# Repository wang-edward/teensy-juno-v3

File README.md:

# teensy-juno
A Teensy 3.x/4.x based polyphonic synthesizer, modelled after the Juno-106

## Features
- 8 Voice polyphony
- Flanger! 
  - Offset, depth, and rate parameters, and presets
- 
- Pulse, Saw, Sub, and noise oscillators
- HPF and LPF with resonance
- ADSR Envelope
- Pan
- Portamento with variable time
- LFO with delay
- PWM modulation
- VCF mod by Envelope, Lfo and Mod Wheel

## Coming soon?
- hardware
- vcf key tracking?
- moog ladder filter emulation (needs teensy 4.0) 
  - based on (www.researchgate.net/publication/220386519_Oscillator_and_Filter_Algorithms_for_Virtual_Analog_Synthesis)
- filter or regular overdrive
## Notes
don't buy this pcb right now (Dec 2021), there are some errors with clearances lol

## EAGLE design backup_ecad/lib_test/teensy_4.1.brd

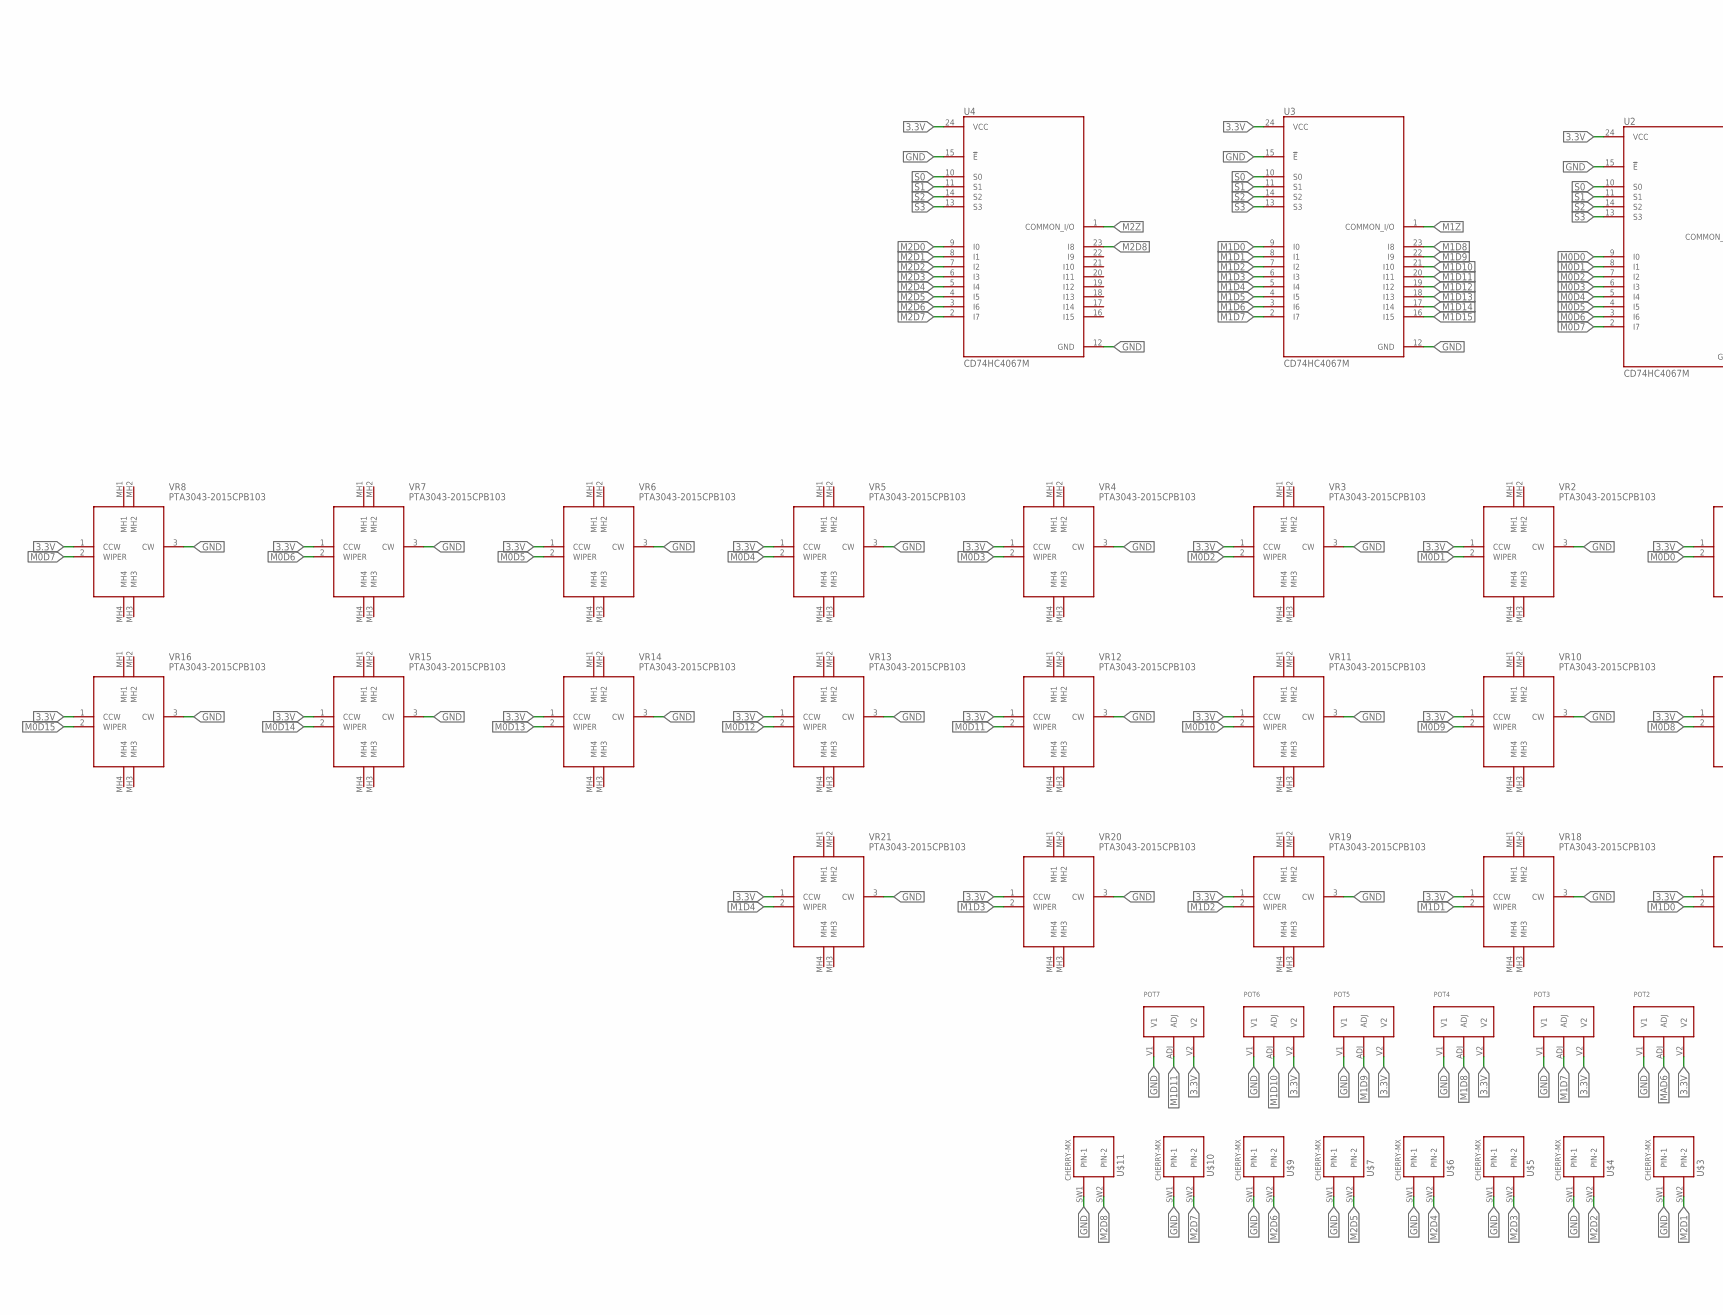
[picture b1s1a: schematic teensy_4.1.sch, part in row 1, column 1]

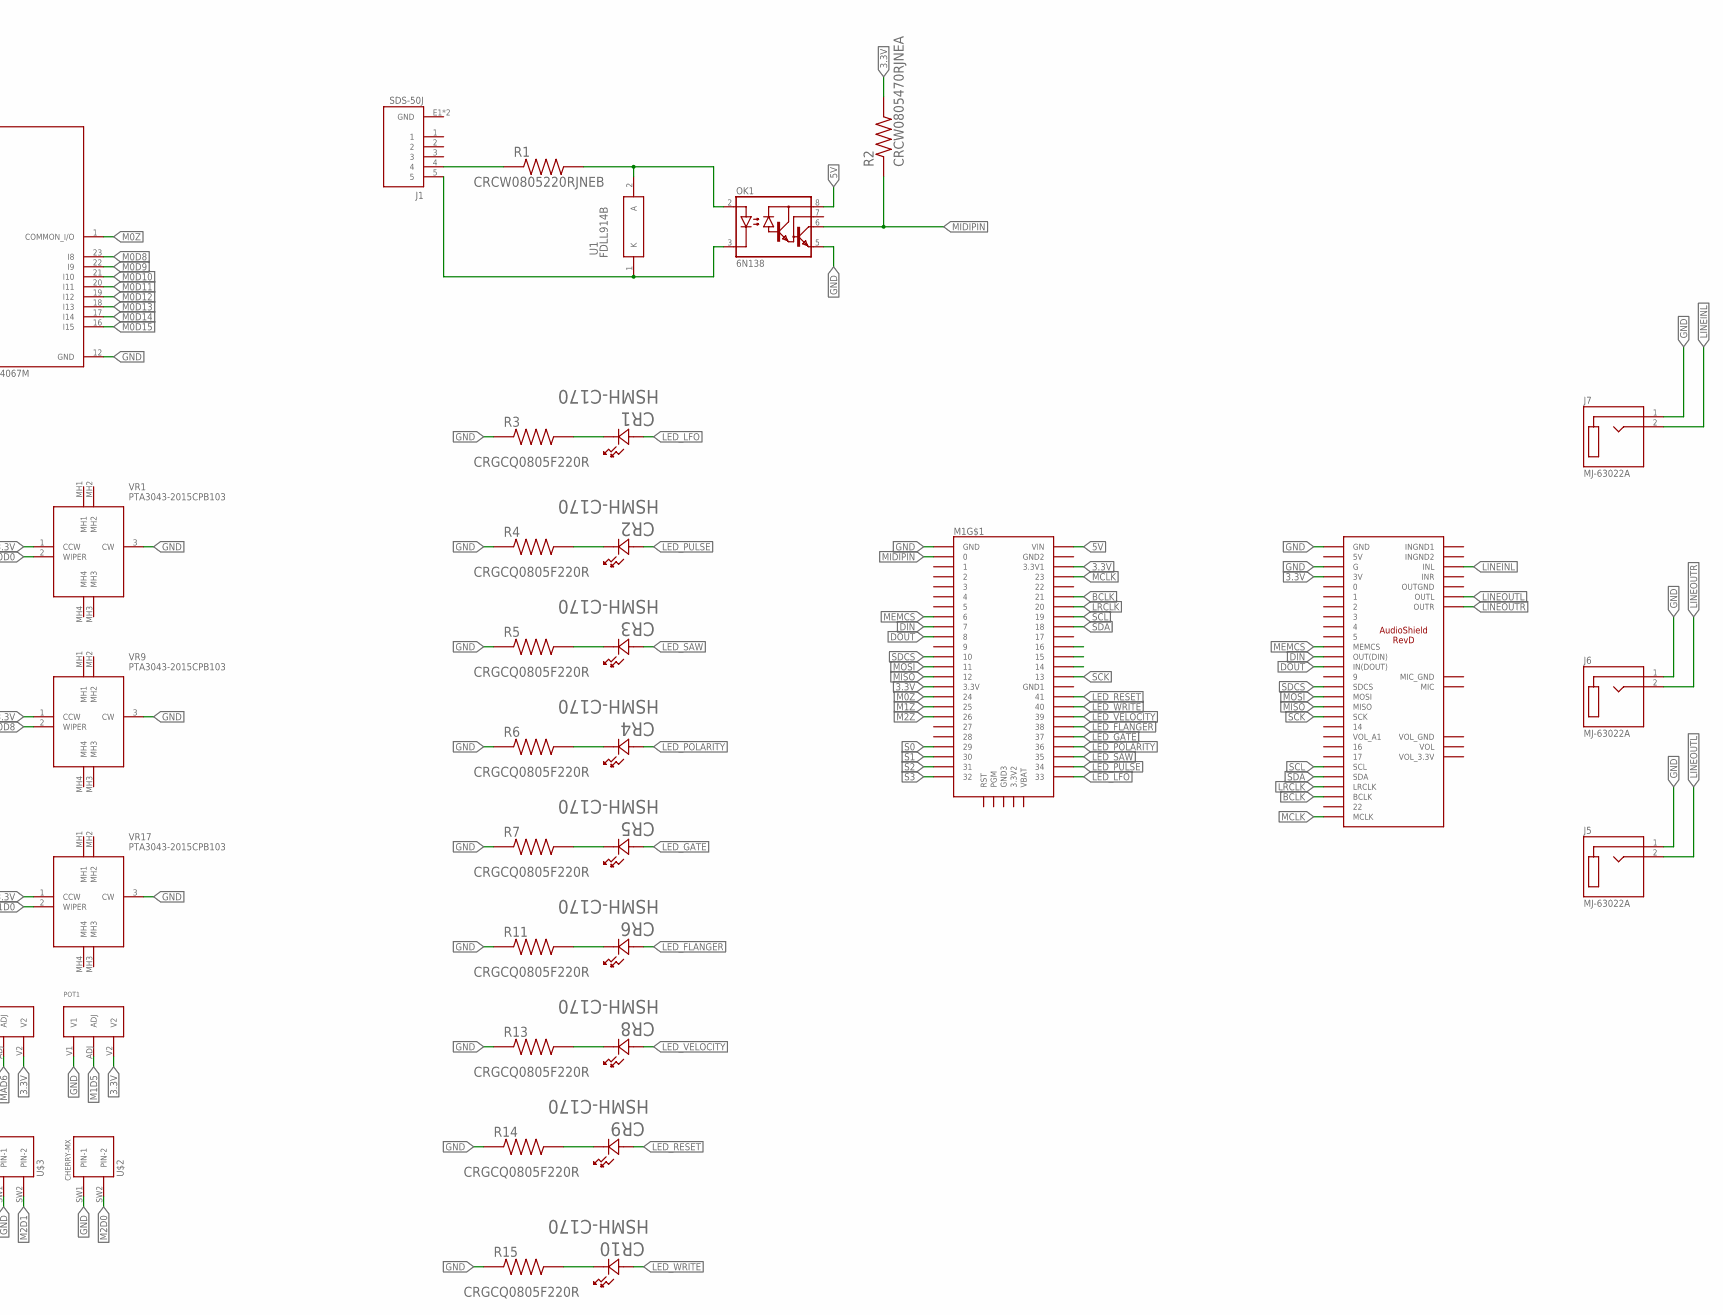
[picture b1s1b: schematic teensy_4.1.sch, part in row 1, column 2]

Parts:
CR1, CR2, CR3, CR4, CR5, CR6, CR8, CR9, CR10: HSMH-C170; LED_HSMX-C170_AVA
J1: SDS-50J; CUI_SDS-50J
J5, J6, J7: MJ-63022A; CUI_MJ-63022A
M1: TEENSY4.1
OK1: 6N138; DIL08
POT1, POT2, POT3, POT4, POT5, POT6, POT7: P0915N_POT; PO915N_POT
R1: CRCW0805220RJNEB; RESC2012X50N
R2: CRCW0805470RJNEA; RESC2012X50N
R3, R4, R5, R6, R7, R11, R13, R14, R15: CRGCQ0805F220R; RESC2012X65N
U1: FDLL914B; SOD-80-2_3P6X1P5_ONS
U2, U3, U4: CD74HC4067M; SOIC127P1030X265-24N
U$1: AUDIOSHIELD-REVD
U$2, U$3, U$4, U$5, U$6, U$7, U$9, U$10, U$11: CHERRY-MX
VR1, VR2, VR3, VR4, VR5, VR6, VR7, VR8, VR9, VR10, VR11, VR12, VR13, VR14, VR15, VR16, VR17, VR18, VR19, VR20, VR21: PTA3043-2015CPB103; PTA30432015CPB103

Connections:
3.3V: M1.3V3 (3.3V), M1.3V3_LO (3.3V1), POT1.V2, POT2.V2, POT3.V2, POT4.V2, POT5.V2, POT6.V2, POT7.V2, R2.2, U2.24 (VCC), U3.24 (VCC), U4.24 (VCC), U$1.3V, VR1.1 (CCW), VR2.1 (CCW), VR3.1 (CCW), VR4.1 (CCW), VR5.1 (CCW), VR6.1 (CCW), VR7.1 (CCW), VR8.1 (CCW), VR9.1 (CCW), VR10.1 (CCW), VR11.1 (CCW), VR12.1 (CCW), VR13.1 (CCW), VR14.1 (CCW), VR15.1 (CCW), VR16.1 (CCW), VR17.1 (CCW), VR18.1 (CCW), VR19.1 (CCW), VR20.1 (CCW), VR21.1 (CCW)
5V: M1.VIN, OK1.8 (VCC)
BCLK: M1.21/A7 (21), U$1.21 (BCLK)
DIN: M1.7, U$1.7 (OUT(DIN))
DOUT: M1.8, U$1.8 (IN(DOUT))
GND: J1.E1 (GND), J1.E2 (GND), J5.1 (SLEEVE), J6.1 (SLEEVE), J7.1 (SLEEVE), M1.GND, OK1.5 (GND), POT1.V1, POT2.V1, POT3.V1, POT4.V1, POT5.V1, POT6.V1, POT7.V1, R3.1, R4.1, R5.1, R6.1, R7.1, R11.1, R13.1, R14.1, R15.1, U2.12 (GND), U2.15 (!E), U3.12 (GND), U3.15 (!E), U4.12 (GND), U4.15 (!E), U$1.G, U$1.GND, U$2.SW1 (PIN-1), U$3.SW1 (PIN-1), U$4.SW1 (PIN-1), U$5.SW1 (PIN-1), U$6.SW1 (PIN-1), U$7.SW1 (PIN-1), U$9.SW1 (PIN-1), U$10.SW1 (PIN-1), U$11.SW1 (PIN-1), VR1.3 (CW), VR2.3 (CW), VR3.3 (CW), VR4.3 (CW), VR5.3 (CW), VR6.3 (CW), VR7.3 (CW), VR8.3 (CW), VR9.3 (CW), VR10.3 (CW), VR11.3 (CW), VR12.3 (CW), VR13.3 (CW), VR14.3 (CW), VR15.3 (CW), VR16.3 (CW), VR17.3 (CW), VR18.3 (CW), VR19.3 (CW), VR20.3 (CW), VR21.3 (CW)
LED_FLANGER: CR6.2, M1.38
LED_GATE: CR5.2, M1.37
LED_LFO: CR1.2, M1.33
LED_POLARITY: CR4.2, M1.36
LED_PULSE: CR2.2, M1.34
LED_RESET: CR9.2, M1.41
LED_SAW: CR3.2, M1.35
LED_VELOCITY: CR8.2, M1.39
LED_WRITE: CR10.2, M1.40
LINEINL: J7.2 (TIP), U$1.INL
LINEOUTL: J5.2 (TIP), U$1.OUTL
LINEOUTR: J6.2 (TIP), U$1.OUTR
LRCLK: M1.20/A6 (20), U$1.20 (LRCLK)
M0D0: U2.9 (I0), VR1.2 (WIPER)
M0D1: U2.8 (I1), VR2.2 (WIPER)
M0D2: U2.7 (I2), VR3.2 (WIPER)
M0D3: U2.6 (I3), VR4.2 (WIPER)
M0D4: U2.5 (I4), VR5.2 (WIPER)
M0D5: U2.4 (I5), VR6.2 (WIPER)
M0D6: U2.3 (I6), VR7.2 (WIPER)
M0D7: U2.2 (I7), VR8.2 (WIPER)
M0D8: U2.23 (I8), VR9.2 (WIPER)
M0D9: U2.22 (I9), VR10.2 (WIPER)
M0D10: U2.21 (I10), VR11.2 (WIPER)
M0D11: U2.20 (I11), VR12.2 (WIPER)
M0D12: U2.19 (I12), VR13.2 (WIPER)
M0D13: U2.18 (I13), VR14.2 (WIPER)
M0D14: U2.17 (I14), VR15.2 (WIPER)
M0D15: U2.16 (I15), VR16.2 (WIPER)
M0Z: M1.24, U2.1 (COMMON_I/O)
M1D0: U3.9 (I0), VR17.2 (WIPER)
M1D1: U3.8 (I1), VR18.2 (WIPER)
M1D2: U3.7 (I2), VR19.2 (WIPER)
M1D3: U3.6 (I3), VR20.2 (WIPER)
M1D4: U3.5 (I4), VR21.2 (WIPER)
M1D5: POT1.ADJ, U3.4 (I5)
M1D6: U3.3 (I6)
M1D7: POT3.ADJ, U3.2 (I7)
M1D8: POT4.ADJ, U3.23 (I8)
M1D9: POT5.ADJ, U3.22 (I9)
M1D10: POT6.ADJ, U3.21 (I10)
M1D11: POT7.ADJ, U3.20 (I11)
M1D12: U3.19 (I12)
M1D13: U3.18 (I13)
M1D14: U3.17 (I14)
M1D15: U3.16 (I15)
M1Z: M1.25, U3.1 (COMMON_I/O)
M2D0: U4.9 (I0), U$2.SW2 (PIN-2)
M2D1: U4.8 (I1), U$3.SW2 (PIN-2)
M2D2: U4.7 (I2), U$4.SW2 (PIN-2)
M2D3: U4.6 (I3), U$5.SW2 (PIN-2)
M2D4: U4.5 (I4), U$6.SW2 (PIN-2)
M2D5: U4.4 (I5), U$7.SW2 (PIN-2)
M2D6: U4.3 (I6), U$9.SW2 (PIN-2)
M2D7: U4.2 (I7), U$10.SW2 (PIN-2)
M2D8: U4.23 (I8), U$11.SW2 (PIN-2)
M2Z: M1.26, U4.1 (COMMON_I/O)
MAD6: POT2.ADJ
MCLK: M1.23/A9 (23), U$1.23 (MCLK)
MEMCS: M1.6, U$1.6 (MEMCS)
MIDIPIN: M1.0/RX (0), OK1.6 (VO), R2.1
MISO: M1.12/MISO (12), U$1.12 (MISO)
MOSI: M1.11/MOSI (11), U$1.11 (MOSI)
unnamed: J1.4, R1.1
unnamed: OK1.2 (A), R1.2, U1.2 (A)
unnamed: J1.5, OK1.3 (C), U1.1 (K)
unnamed: CR2.1, R4.2
unnamed: CR1.1, R3.2
unnamed: CR3.1, R5.2
unnamed: CR4.1, R6.2
unnamed: CR5.1, R7.2
unnamed: CR6.1, R11.2
unnamed: CR8.1, R13.2
unnamed: CR9.1, R14.2
unnamed: CR10.1, R15.2
S0: M1.29, U2.10 (S0), U3.10 (S0), U4.10 (S0)
S1: M1.30, U2.11 (S1), U3.11 (S1), U4.11 (S1)
S2: M1.31/A12 (31), U2.14 (S2), U3.14 (S2), U4.14 (S2)
S3: M1.32, U2.13 (S3), U3.13 (S3), U4.13 (S3)
SCK: M1.13/SCK (13), U$1.13 (SCK)
SCL: M1.19/A5/SCL (19), U$1.19 (SCL)
SDA: M1.18/A4/SDA (18), U$1.18 (SDA)
SDCS: M1.10/CS (10), U$1.10 (SDCS)

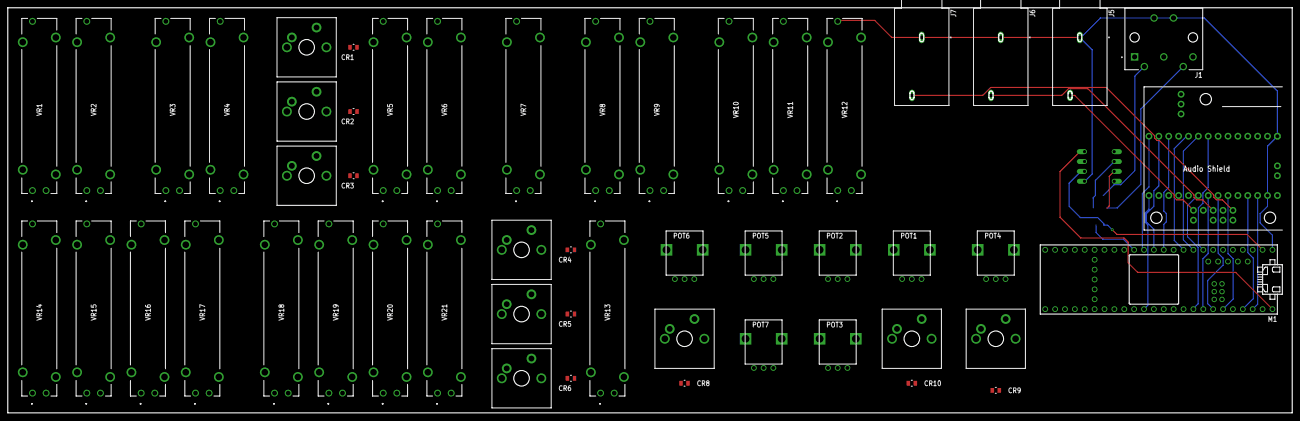
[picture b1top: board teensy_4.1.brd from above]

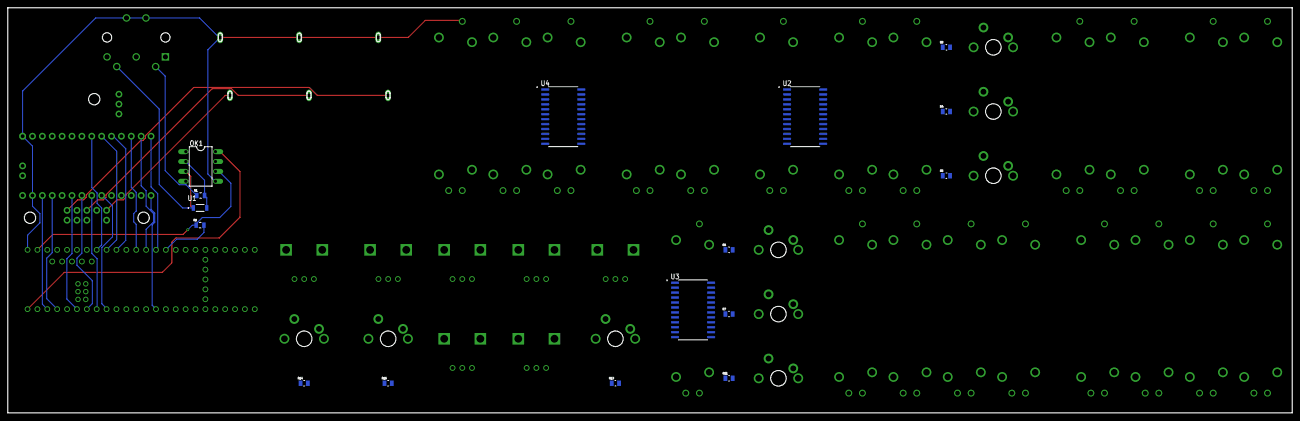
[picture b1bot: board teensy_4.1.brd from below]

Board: 2 copper layers, 330.2 x 104.1 mm, 68 parts (16 on the bottom side), 83 nets.

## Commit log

2021-05-16 starter code (poly note handling) from jmechnich
2021-05-16 modifying starter code
2021-05-17 built new architecture and started on oscillator control
2021-05-18 finished outline of midi and note handling, still broken
2021-05-21 fixed lots of bugs (no more error messages) but still doesnt work
2021-05-25 added new arch diagram and some more attempts at fixing
2021-05-30 made a test file and realized i had to set the waveform
2021-05-30 2 weeks of debugging to find out i forgot to set envOn = true LMAOOO
2021-05-31 added separate control change file and changed squares to pulses
2021-06-01 changed more square to pulse
2021-06-18 some bug fixes idk
2021-06-19 changed waveforms to AudioSynthWaveform from AudioSynthWaveformModulated
2021-06-20 built pd control panel and testing chorus in mono
2021-06-26 added original synth manual layout for reference
2021-06-26 reorganized files and changed pulsePWM to sub (prep for adding chorus)
2021-06-27 tried to reformat code to make it modular and changing chorus to flanger
2021-06-28 lots of bug fixes, feeling pretty good
2021-06-28 refactoring, fixed all bugs but doesn't make any sound
2021-07-02 3d try (no flanger) didnt work
2021-07-04 reformatting working version
2021-07-12 added 4k resolution of architecture
2021-07-12 added pd interface
2021-07-19 dont remember lol
2021-07-28 progress! got flanger to work but still buggy: notes keep playing forever
2021-07-31 figured out what flanger passthru does and also did updateEnvmode but still buggy
2021-08-01 more debugging ig
2021-08-01 more debugging and update contorl panel
2021-08-01 FIXED THE BUG!!!!!!!!! had to do with synth architecture, got rid of gate functionality to fix it (who cares)
2021-08-02 fixed bug in main
2021-08-02 update contorl change and uncomment some pan stuff
2021-08-02 working on control panel and some code optimization! going to tennis now pog
2021-08-03 working on oscillator control, sub and noise levels
2021-08-03 fixed oscillator select (i think i forgot break statements)
2021-08-03 update tha readme! #demontime 😈
2021-08-05 worked on sub and noise level bug but not sure if the noise is fixed
2021-08-05 fixed noise and sub level bug
2021-08-05 routed env output to lpf (not sure if this works)
2021-08-06 MORE TESTING OF LPF ENV MOD,
    the filter is definitely getting modulated, but i think it's getting modulated by the oscillators instead of the raw signal from the envelope
2021-08-07 got portamento working!
2021-08-07 update readme cuz portamento works now ! :banana:
2021-08-08 LPF ENVELOPE WORKS! only problem is it can make lpf freq go above audio sample rate which makes noise
2021-08-09 added manual and *partially* updated synth arch for LFO modulation
2021-08-11 working on lfo
2021-08-26 work from vacation
2021-08-26 got pitch modulation working in osc test
2021-08-27 GOT OSC MODULATION WORKING! think it was something with offset
2021-08-27 worked on pwm and lfo modulation and added some midi files to test with
2021-08-27 we making gains 💪🏿
2021-08-28 added lfo pwm and vcf env mod inversion switches, also routed vcf modulation and control changes
2021-08-28 got vcf modulation working, have to test different values for vcfEnvModLevel (100 rn)
2021-08-30 got vcf env kind of working, realised i need a seperate mod source for each voice :/
2021-08-30 added a lpfmodmixer for each voice and started using "lpf"instead of "vcf"
2021-08-31 done lfo delay, very close to finishing software (only last bug is filter clipping)
2021-09-02 fix filter clipping, turns out logarithms are useful
2021-09-02 update architecture so that delay affects pitch and pwm
2021-09-06 more pictures for circuit planning
2021-09-13 made preset class
2021-09-13 moved lpf mod variables to global file
2021-09-14 halfway through presets & update todo.txt
2021-09-14 finished presets architecture, still need to do in control_change.h
2021-09-14 forgot to press save, same desc as above
2021-09-16 cleaning up files
2021-09-16 cleaning up pics
2021-09-16 add pic of architecture to readme
2021-09-16 more pics!
2021-09-19 started working on schematic design
2021-09-22 working on json preset storage
2021-09-22 removed sub/noiseON and started json
2021-09-23 sd card json (not tested)
2021-10-02 more pics
2021-10-22 started working on presets
    also some sd card code but not sure if it does anything
2021-11-13 autorouter draft?
2021-11-15 backups and documentation
2021-11-18 Create bom
2021-11-28 started working on analog controls
2021-12-01 removed json, added mux, other small fixes
2021-12-02 added midi port capability!
2021-12-03 testing some reading, might move to platformio
2021-12-05 trying to add parameter class
2021-12-05 trying to add update_function to parameter object
2021-12-06 adding analog control for sliders
2021-12-10 finished hardware pog!!!
2021-12-10 sheeeeeeeeeeeeeeeeeeeeeeeeeeeeeeeeeeeeeeeeesh
2021-12-12 some multiplexer testing
2021-12-16 replaced lpf with ladder filter
2021-12-20 still broken idkasdalshd
2022-01-05 added documentation
2022-01-06 added pictures

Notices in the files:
parts and their libraries:
COPYRIGHT: Copyright (C) 2021 Ultra Librarian. All rights reserved.
